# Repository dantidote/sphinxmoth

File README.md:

# Sphinxmoth

### The little board that answers the iSphynxII: a working flash mod for FireWire iPods (1st/2nd gen)

An **active FPGA interposer** that lets flash storage (CF, or SD behind an adapter) fully replace the 1.8″ hard drive in a **1st/2nd-generation
iPod**: boot, standalone playback, **and full-speed FireWire restore + iTunes sync**.

This is the first time in the ~25 years since these iPods shipped
that all of that works at once on flash storage. Passive adapters never could, and
it turns out they never could have. The reason was documented by Texas
Instruments in 2001.

A note on qualifications: I had none. This is the first PCB I've ever had
made, I leaned on the autorouter more than any self-respecting layout
engineer would admit, and before this project I'd never programmed an FPGA.
This board isn't pretty; it was never meant to be. It exists to answer one
question: is this possible at all?

| | |
|---|---|
|  |  |

*The assembled v1 board: FPGA side and CF side. And the point of it all:*

<p align="center"><i>A 1.8 GB file at roughly 15 MB/s over FireWire, through the bridge. No, the
1st gen can't play it. That's not the point.</i></p>

## Buying an assembled board

Sphinxmoth is open source and stays that way: the gerbers, BOM, gateware and
a hardware-validated bitstream are all in this repo, under licenses (MIT and
CERN-OHL-P-2.0) that let you build your own, and sell them if you want to.
Please do.

If you would rather not order a PCB, source a MachXO2, and go find a JTAG
probe, I sell **pre-assembled, pre-flashed boards** at
**[wunkuslabs.com](https://wunkuslabs.com/products/sphinxmoth)**.

## Why the cheap green CF/IDE adapters never worked

FireWire-era iPods (1G/2G, and the 3G) use TI's **TSB43AA82 "iSphynxII"**
FireWire-to-ATA bridge. From TI's own *TSB43AA82 Storage Reference Design*:

> It should be noted that iSphynxII does not implement the 16-bit CRC value
> required at the end of ATA ultraDMA transfers. There are two ways to deal
> with this. The first is to use HDDs that allow transfers to continue even if
> the correct CRC value is not received. The second is to insert an ASIC/PLD
> between iSphynxII and the HDD that calculates the CRC as the transfer is
> taking place and drives it to the drive at the appropriate time. This
> reference design assumes the HDD does not require the CRC.

Apple took TI's first option: the original Toshiba 1.8″ drives tolerate the
missing CRC. **Every CF card enforces it.** So the moment a flash device sees
an Ultra-DMA burst from the iSphynxII, it (correctly) rejects the transfer with
an interface-CRC error, and no passive adapter can ever fix that, because the
CRC simply isn't on the wire.

**This project is the "ASIC/PLD between iSphynxII and the HDD" that TI
described, built 25 years later.** A Lattice MachXO2 sits in the datapath,
re-originates every UDMA burst, and supplies the CRC the iSphynxII omits.

But the CRC is only the first wall. Credit to Reddit user **SquashHour9940**,
whose excellent investigation
([*Further research about flash modified iPod 1st/2nd Gen syncing problem*](https://www.reddit.com/r/ipod/comments/18fujac/further_research_about_flash_modified_ipod_1st2nd/))
independently mapped two more layers:

2. **Removable vs. fixed media**: consumer CF cards report themselves as
   *removable media*; the iPod firmware and iTunes want a *fixed disk*.
   Industrial CF cards (fixed-disk firmware) get past this gate; consumer
   cards don't.
3. **The TSB43AA82 falls back to slow PIO when it detects a CF card**:
   staged 1 MB at a time through the iPod's tiny SRAM, capping passive-adapter
   FireWire transfers around 300 KB/s even when everything else works.

And our bring-up found a fourth layer nobody had hit before, because nobody
had gotten this far:

4. **The PP5002 CPU (the retail OS) is a DMA host too**: its UDMA write
   strobes are electrically hostile (ringing, data-dependent crosstalk) and
   corrupted the filesystem on every standalone boot until this bridge learned
   to detect that master and quietly demote it to PIO.

This bridge defeats all four: it originates the missing CRC, rewrites the
card's IDENTIFY on the wire (media type and DMA capabilities, per master;
a removable or CFA-signature word 0 becomes a classic fixed-disk value,
checksum corrected), keeps the DMA path alive at full speed, and gives
each of the iPod's two very different bus masters the bus discipline it
actually needs. The fixed-disk rewrite has been tested end-to-end with a
retail Lexar Professional 800x (32 GB, UDMA 7), the exact card class the
community documented as removable-reporting: it restores and syncs
through the bridge like any industrial card.

## Status

| | |
|---|---|
| **v1 board** (CF slot, `board/`) | **Working.** Boots, plays, restores, syncs. Reads 19 MB/s, writes 4.6 MB/s over FireWire. Running a 256 GB SD (via FC1307A CF adapter) today. |
| Validated bitstream | `releases/v1.0-first-music/` (build outputs are not run-deterministic; this exact binary is the hardware-proven one) |
| **v2** (native microSD) | **Being considered.** microSD would be nice, but at first glance it needs a larger/more expensive FPGA (the v1 XO2-2000 is 89% full and the disk logic moves on-chip; the draft targets an XO2-7000). Exploratory work lives on the [`v2-native-sd`](../../tree/v2-native-sd) branch: unfabbed, unvalidated, promise-free. **Do not build it.** |

Tested on: iPod 1st gen (firmware 1.5), Transcend industrial 2 GB CF,
FC1307A SD-CF adapter + 256 GB SD, Mac OS X 10.6 + iTunes over FireWire.
2G/3G iPods use the same TSB43AA82 and *should* work; reports welcome.

## Rockbox

Rockbox runs on a Sphinxmoth iPod, with two board-specific wrinkles: the
Rockbox 4.0 release crashes at boot on every 1G/2G (an unaligned store in
the PP5002 scheduler, fixed upstream after 4.0), and Rockbox's stock IDE
timing is too fast for the `v1.1-mg132-fix3b` bridge image, which adds
about 45 ns to every register read through its PIO synchroniser (init fails
with `ATA error: -11` or `-32`). Newer bridge images pass PIO through the
raw pads and need nothing but the crash fix.

Everything Rockbox-related lives in its own repo:
[**rockbox-pp5002-flash**](https://github.com/dantidote/rockbox-pp5002-flash):
the ATA driver patch, tested builds for boards already in the field on
fix3b, and a workflow that rebuilds them on each upstream Rockbox release.
The same files are served from [wunkuslabs.com/guide](https://wunkuslabs.com/guide#rockbox).

## How it works (the short version)

The FPGA discovered during bring-up that it serves **three masters**, and it
gives each a different personality:

| Master | How it's detected | What it gets |
|---|---|---|
| **iSphynxII** (FireWire) | never issues `EXECUTE DIAGNOSTIC` | Full UDMA2 bridge: bursts re-timed through a FIFO, **end-of-burst CRC generated**, multi-burst writes, a deliberately "bouncy" flow-control throttle (it abandons bursts on long clean pauses) |
| **PP5002** (retail OS) | opens with `C90 EXECUTE DIAGNOSTIC` | IDENTIFY patched in flight (DMA capability words zeroed, checksum fixed) → the OS falls back to PIO `READ/WRITE MULTIPLE` through a transparent passthrough |
| **CF card** | n/a | Always runs UDMA2, regardless of what either host negotiated (`SET FEATURES` sector-count byte rewritten on the wire) |

Plus the small in-flight surgeries each master demanded: BSY served for status
polls mid-command, CS/DA forced idle at the card during bridged bursts, strict
data setup/hold on every strobe edge, spec-ordered burst termination, and
STANDBY/SLEEP commands rewritten to CHECK POWER MODE (retail cards honor them,
then never wake the way the OS expects; the original drive woke transparently). The
testbenches encode all of it: the card model sector-terminates, pauses,
checks CRC and enforces tSS; the host model parks on the status register,
polls, and rings its strobe line. Every cruelty in the sims reproduced a bug
first found on real hardware during a two-day, fourteen-bug bring-up.

## Building it

Or skip it: assembled, flashed and tested boards are
[for sale](https://wunkuslabs.com/products/sphinxmoth).

**Board (v1):** upload `board/ipod-cf-udma-gerbers.zip` to any fab (2 layer,
53×72 mm, 1.6 or 0.8 mm). CF socket (J2) is on the BACK; everything else on
the front. `board/BOM.csv` + `board/ipod-cf-udma-pos.csv` for assembly.

**Bitstream:** Lattice Diamond 3.14, `cd diamond && pnmainc rebuild.tcl` →
`impl1/ipodboard_impl1.jed`. Or just flash `releases/v1.0-first-music/`.

**Programming:** Tag-Connect TC2030-IDC-NL pads (J3, zero height) to any
JTAG probe Diamond Programmer / openFPGALoader speaks. The MachXO2 configures
from internal flash; program once, done.

**Power:** bus-powered from the iPod's 3.3 V. J6 shunt selects iPod (1-2) or
bench USB-C (2-3); never both. The green LED blips a slow heartbeat when idle
and flashes while data is moving through the bridge. The UART header (J5, 115200 8N1) streams the
gateware's event log; if something misbehaves, that log is the microscope
this whole project was debugged through.

**Simulation:** Icarus Verilog: `cd gateware && iverilog -g2012 -DSIM -I rtl
-o wr.vvp sim/tb_full_write.v rtl/*.v && vvp wr.vvp` (likewise
`tb_full_read.v`).

## Repository layout

| Path | Contents |
|---|---|
| `board/` | v1 board: KiCad project, fabbed gerbers, BOM, schematic PDF, DRC/ERC |
| `gateware/rtl/` | the bridge RTL (`interposer_top` + engines) |
| `gateware/sim/` | hardware-calibrated torture testbenches |
| `diamond/` | Lattice Diamond build project |
| `releases/` | hardware-validated bitstreams |
| `v2-native-sd` branch | exploratory native-microSD v2: board draft, `ata_device`/`sd_host` cores, design doc |

## Known v1 errata

- J2 pin 39 (−CSEL) must be grounded (already fixed in these gerbers).
- J2 pins 45/46 (−DASP/−PDIAG) float; some cards may care (10 k pull-ups to
  3.3 V recommended).
- The USB-C shield holes share the CF socket's courtyard; desoldering J4
  heat-stresses socket joints (ask us how we know). v2 deletes both parts.
- DD-bus ↔ control-line crosstalk exists at the margins; the gateware routes
  around it (PIO for the PP5002), v2 adds proper guarding.

## Credits

- **SquashHour9940** (r/ipod): the fixed-disk/removable-media and
  TSB43AA82-PIO-fallback research that mapped layers 2 and 3:
  https://www.reddit.com/r/ipod/comments/18fujac/further_research_about_flash_modified_ipod_1st2nd/
- Texas Instruments, for documenting in 2001 exactly which chip to blame
  and exactly what to build about it.
- [freerouting](https://github.com/freerouting/freerouting): the open-source
  autorouter that closed every net on both boards.

## License

Gateware and software: MIT. Hardware (schematics, board files, gerbers):
CERN-OHL-P-2.0. No warranty; a 25-year-old iPod is involved.

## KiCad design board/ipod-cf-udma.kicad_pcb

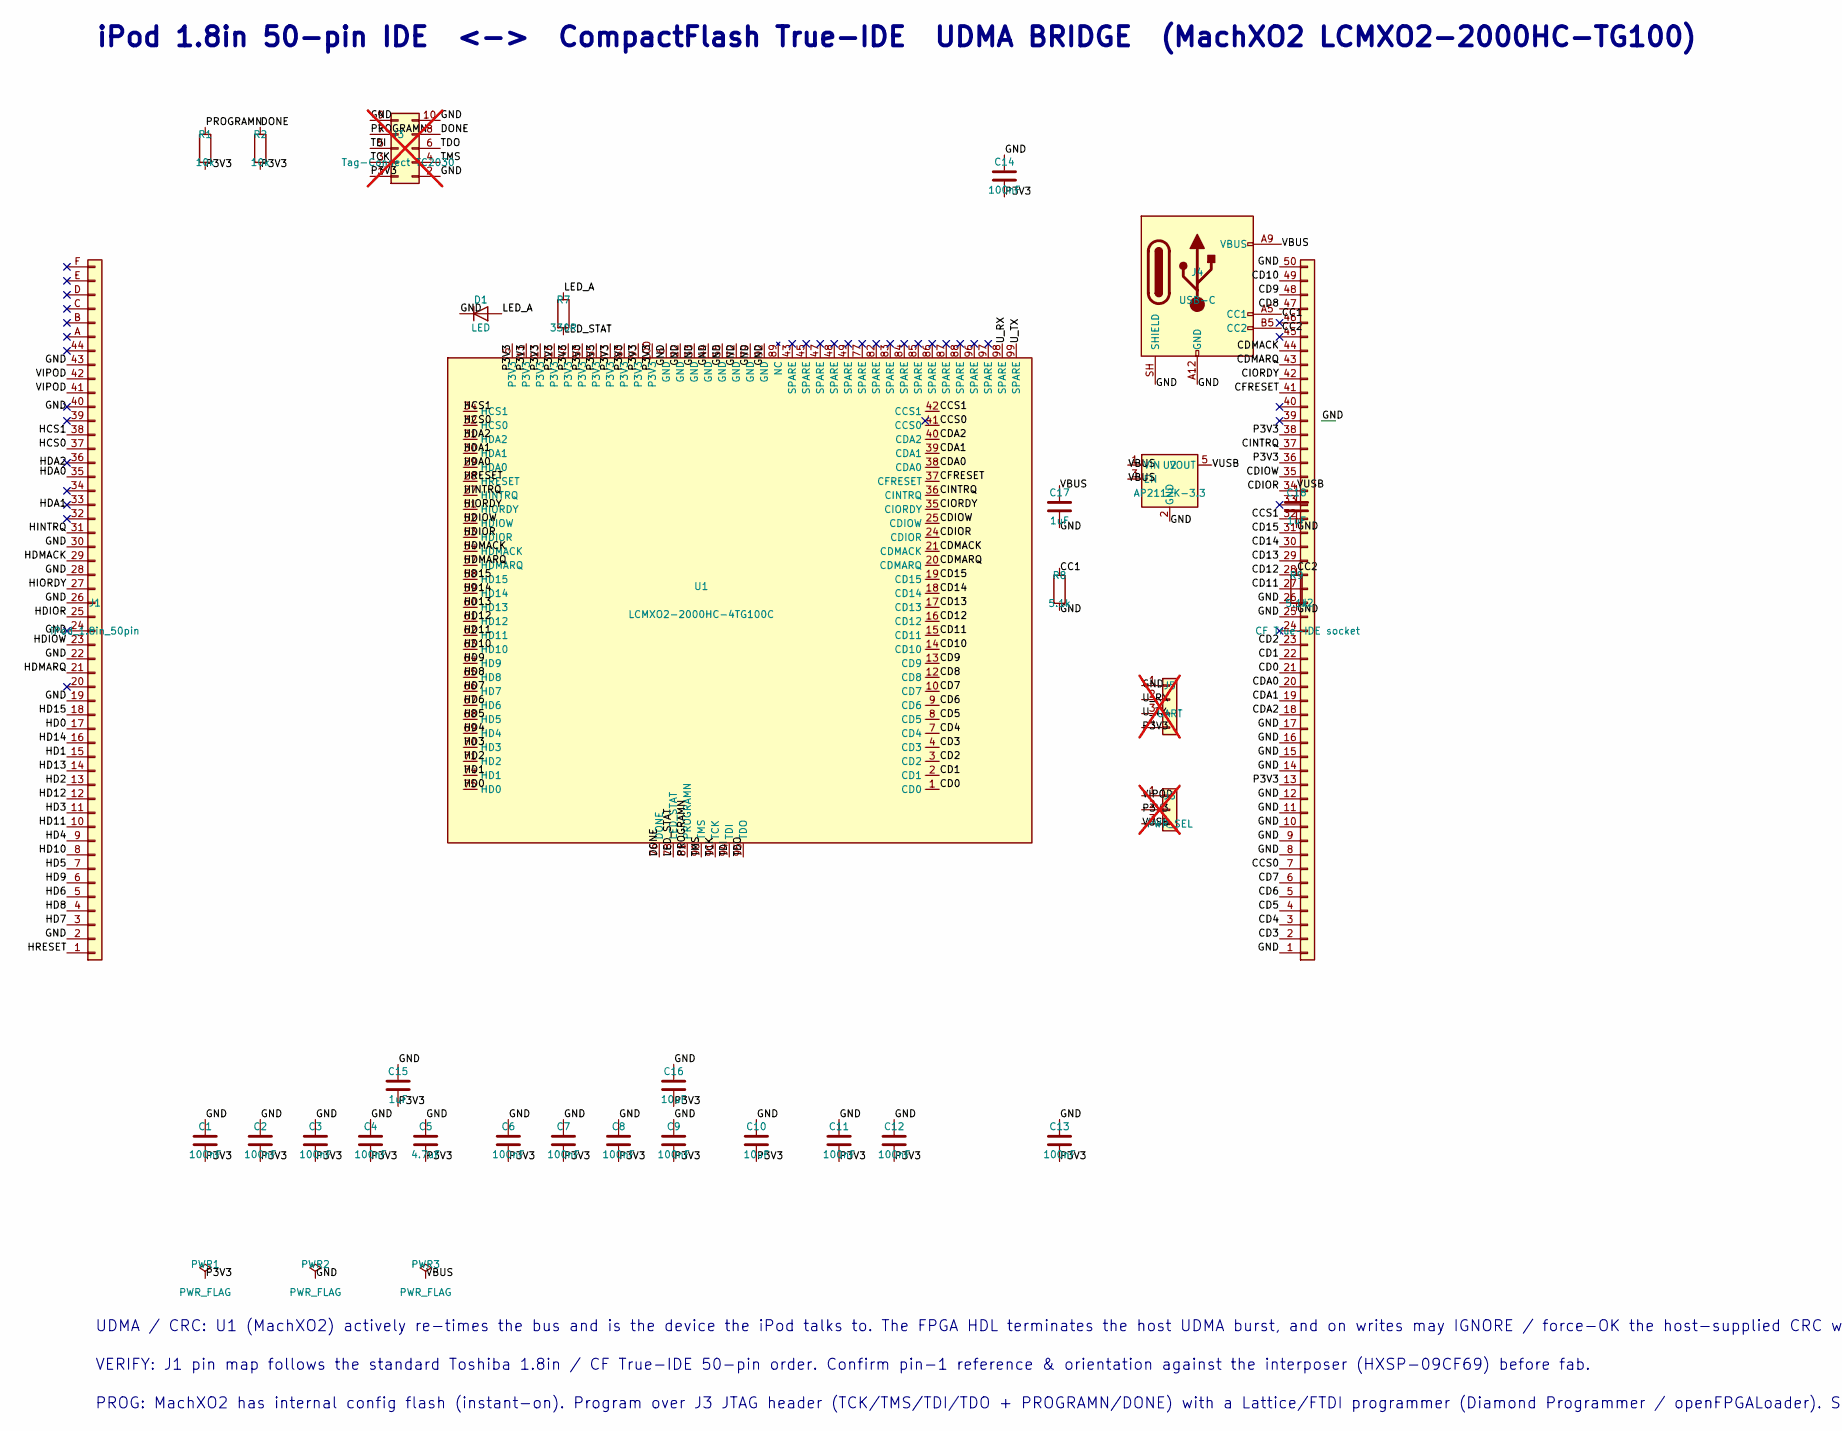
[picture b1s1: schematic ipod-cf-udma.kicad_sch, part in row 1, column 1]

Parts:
C1, C2, C3, C4, C6, C7, C8, C9, C11, C12, C13, C14: 100nF; C_0402_1005Metric; MPN CL05B104KO5NNNC
C5: 4.7uF; C_0603_1608Metric; MPN CL10A475KO8NNNC
C10, C16: 10uF; C_0805_2012Metric; MPN C2012X5R1E106K125AB
C15, C17, C18: 1uF; C_0402_1005Metric; MPN CL05A105KA5NNNC
D1: LED; LED_0603_1608Metric; MPN 150060GS75000
J1: iPod_1.8in_50pin; MPN SPECIALTY-iPod-1.8in-50pin
J2: CF True-IDE socket; CF-Card_3M_N7E50-E516xx-30; MPN N7E50-E516PK-30
J3: Tag-Connect TC2030; Tag-Connect_TC2030-IDC-NL_2x03_P1.27mm_Vertical; MPN DNP-padsonly; not fitted
J4: USB-C; USB_C_Receptacle_GCT_USB4125-xx-x_6P_TopMnt_Horizontal; MPN USB4125-GF-A-0190
J5: UART; PinHeader_1x04_P1.27mm_Vertical_SMD_Pin1Left; MPN DNP-optional-header; not fitted
J6: PWR_SEL; PinHeader_1x03_P1.27mm_Vertical_SMD_Pin1Left; MPN DNP-solderjumper; not fitted
PWR1, PWR2, PWR3: PWR_FLAG
R1, R2: 10k; R_0402_1005Metric; MPN CRCW040210K0FKED
R7: 330R; R_0402_1005Metric; MPN RC0402FR-07330RL
R8, R9: 5.1k; R_0402_1005Metric; MPN RC0402FR-075K1L
U1: LCMXO2-2000HC-4TG100C; TQFP-100_14x14mm_P0.5mm; MPN LCMXO2-2000HC-4TG100C
U2: AP2112K-3.3; SOT-23-5; MPN AP2112K-3.3TRG1

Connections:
CC1: J4.A5 (CC1), R8.1
CC2: J4.B5 (CC2), R9.1
CCS0: J2.7, U1.41 (CCS0)
CCS1: J2.32, U1.42 (CCS1)
CD0: J2.21, U1.1 (CD0)
CD1: J2.22, U1.2 (CD1)
CD2: J2.23, U1.3 (CD2)
CD3: J2.2, U1.4 (CD3)
CD4: J2.3, U1.7 (CD4)
CD5: J2.4, U1.8 (CD5)
CD6: J2.5, U1.9 (CD6)
CD7: J2.6, U1.10 (CD7)
CD8: J2.47, U1.12 (CD8)
CD9: J2.48, U1.13 (CD9)
CD10: J2.49, U1.14 (CD10)
CD11: J2.27, U1.15 (CD11)
CD12: J2.28, U1.16 (CD12)
CD13: J2.29, U1.17 (CD13)
CD14: J2.30, U1.18 (CD14)
CD15: J2.31, U1.19 (CD15)
CDA0: J2.20, U1.38 (CDA0)
CDA1: J2.19, U1.39 (CDA1)
CDA2: J2.18, U1.40 (CDA2)
CDIOR: J2.34, U1.24 (CDIOR)
CDIOW: J2.35, U1.25 (CDIOW)
CDMACK: J2.44, U1.21 (CDMACK)
CDMARQ: J2.43, U1.20 (CDMARQ)
CFRESET: J2.41, U1.37 (CFRESET)
CINTRQ: J2.37, U1.36 (CINTRQ)
CIORDY: J2.42, U1.35 (CIORDY)
DONE: J3.8, R2.1, U1.76 (DONE)
GND: C1.1, C2.1, C3.1, C4.1, C5.1, C6.1, C7.1, C8.1, C9.1, C10.1, C11.1, C12.1, C13.1, C14.1, C15.1, C16.1, C17.2, C18.2, D1.1 (K), J1.2, J1.19, J1.22, J1.24, J1.26, J1.28, J1.30, J1.40, J1.43, J2.1, J2.8, J2.9, J2.10, J2.11, J2.12, J2.14, J2.15, J2.16, J2.17, J2.25, J2.26, J2.39, J2.50, J3.2, J3.9, J3.10, J4.A12 (GND), J4.B12 (GND), J4.SH (SHIELD), J5.1, PWR2.1, R8.2, R9.2, U1.6 (GND), U1.22 (GND), U1.33 (GND), U1.44 (GND), U1.56 (GND), U1.72 (GND), U1.79 (GND), U1.92 (GND), U2.2 (GND)
HCS0: J1.37, U1.32 (HCS0)
HCS1: J1.38, U1.34 (HCS1)
HD0: J1.17, U1.75 (HD0)
HD1: J1.15, U1.74 (HD1)
HD2: J1.13, U1.71 (HD2)
HD3: J1.11, U1.70 (HD3)
HD4: J1.9, U1.69 (HD4)
HD5: J1.7, U1.68 (HD5)
HD6: J1.5, U1.67 (HD6)
HD7: J1.3, U1.66 (HD7)
HD8: J1.4, U1.65 (HD8)
HD9: J1.6, U1.64 (HD9)
HD10: J1.8, U1.63 (HD10)
HD11: J1.10, U1.62 (HD11)
HD12: J1.12, U1.61 (HD12)
HD13: J1.14, U1.60 (HD13)
HD14: J1.16, U1.59 (HD14)
HD15: J1.18, U1.58 (HD15)
HDA0: J1.35, U1.29 (HDA0)
HDA1: J1.33, U1.30 (HDA1)
HDA2: J1.36, U1.31 (HDA2)
HDIOR: J1.25, U1.53 (HDIOR)
HDIOW: J1.23, U1.52 (HDIOW)
HDMACK: J1.29, U1.54 (HDMACK)
HDMARQ: J1.21, U1.57 (HDMARQ)
HINTRQ: J1.31, U1.27 (HINTRQ)
HIORDY: J1.27, U1.51 (HIORDY)
HRESET: J1.1, U1.28 (HRESET)
LED_A: D1.2 (A), R7.1
LED_STAT: R7.2, U1.78 (LED_STAT)
P3V3: C1.2, C2.2, C3.2, C4.2, C5.2, C6.2, C7.2, C8.2, C9.2, C10.2, C11.2, C12.2, C13.2, C14.2, C15.2, C16.2, J2.13, J2.36, J2.38, J3.1, J5.4, J6.2, PWR1.1, R1.2, R2.2, U1.5 (P3V3), U1.11 (P3V3), U1.23 (P3V3), U1.26 (P3V3), U1.46 (P3V3), U1.50 (P3V3), U1.55 (P3V3), U1.73 (P3V3), U1.80 (P3V3), U1.93 (P3V3), U1.100 (P3V3)
PROGRAMN: J3.7, R1.1, U1.81 (PROGRAMN)
TCK: J3.3, U1.91 (TCK)
TDI: J3.5, U1.94 (TDI)
TDO: J3.6, U1.95 (TDO)
TMS: J3.4, U1.90 (TMS)
U_RX: J5.2, U1.98 (SPARE)
U_TX: J5.3, U1.99 (SPARE)
VBUS: C17.1, J4.A9 (VBUS), J4.B9 (VBUS), PWR3.1, U2.1 (VIN), U2.3 (EN)
VIPOD: J1.41, J1.42, J6.1
VUSB: C18.1, J6.3, U2.5 (VOUT)

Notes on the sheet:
iPod 1.8in 50-pin IDE <-> CompactFlash True-IDE UDMA BRIDGE (MachXO2 LCMXO2-2000HC-TG100)
UDMA / CRC: U1 (MachXO2) actively re-times the bus and is the device the iPod talks to. The FPGA HDL terminates the host UDMA burst, and on writes may IGNORE / force-OK the host-supplied CRC while regenerating a correct CRC toward the CF card. A purely passive adapter CANNOT do this - that is why a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
VERIFY: J1 pin map follows the standard Toshiba 1.8in / CF True-IDE 50-pin order. Confirm pin-1 reference & orientation against the interposer (HXSP-09CF69) before fab.
PROG: MachXO2 has internal config flash (instant-on). Program over J3 JTAG header (TCK/TMS/TDI/TDO + PROGRAMN/DONE) with a Lattice/FTDI programmer (Diamond Programmer / openFPGALoader). Single 3.3V rail, bus-powered from host (J1.13/38). I/O pin assignment is a starting point - lock final pins in D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

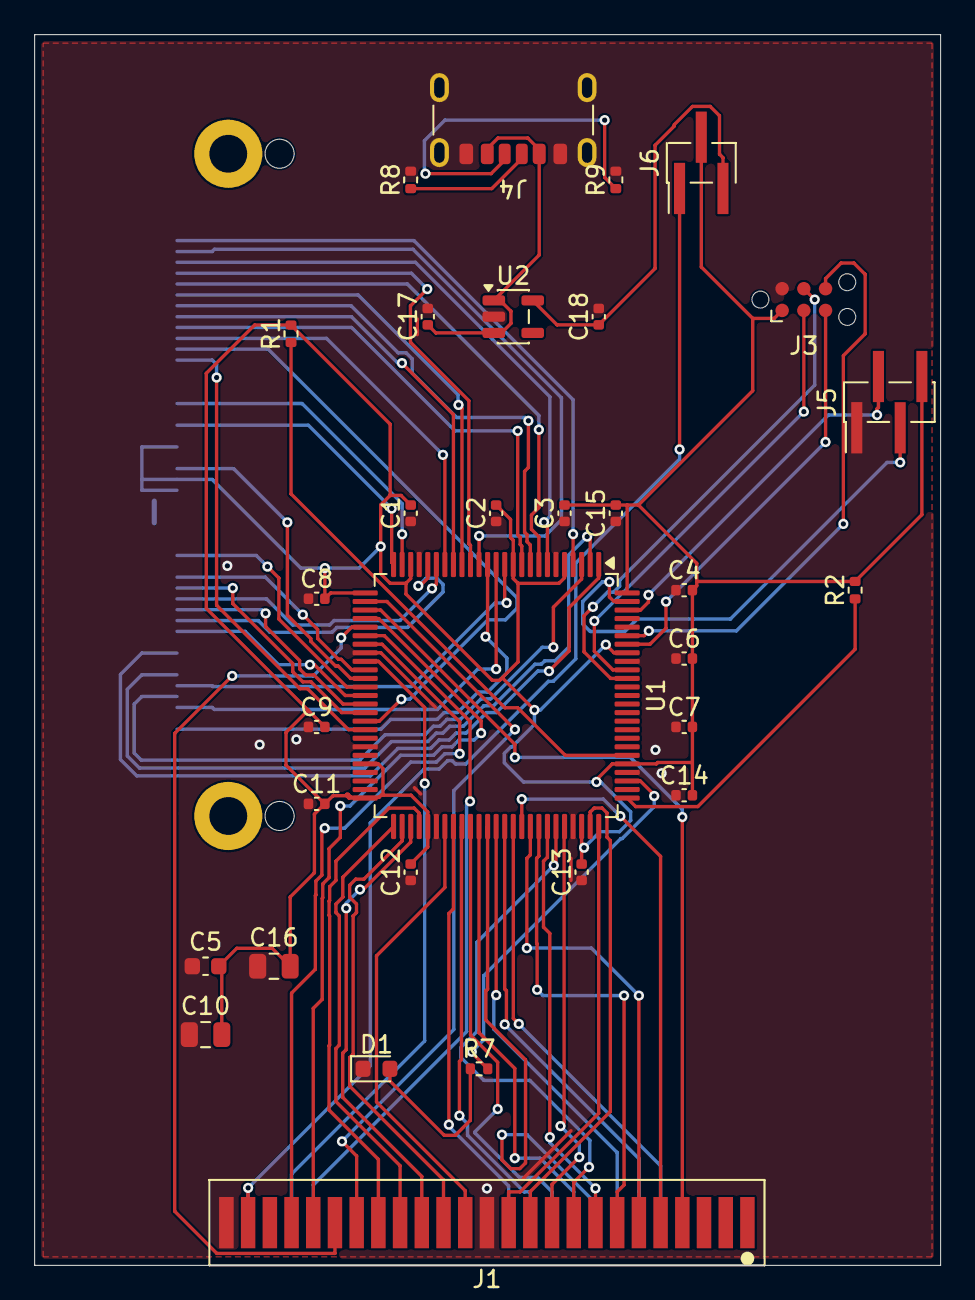
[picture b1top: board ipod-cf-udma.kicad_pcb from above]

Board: 2 copper layers, 53.0 x 72.0 mm, 32 parts (1 on the bottom side), 73 nets.

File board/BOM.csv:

"Refs","Value","Footprint","MPN","Qty"
"C1-C4,C6-C9,C11-C14","100nF","Capacitor_SMD:C_0402_1005Metric","CL05B104KO5NNNC","12"
"C5","4.7uF","Capacitor_SMD:C_0603_1608Metric","CL10A475KO8NNNC","1"
"C10,C16","10uF","Capacitor_SMD:C_0805_2012Metric","C2012X5R1E106K125AB","2"
"C15,C17,C18","1uF","Capacitor_SMD:C_0402_1005Metric","CL05A105KA5NNNC","3"
"D1","LED","LED_SMD:LED_0603_1608Metric","150060GS75000","1"
"J1","iPod_1.8in_50pin","interposer:iPod_1.8in_50pin","SPECIALTY-iPod-1.8in-50pin","1"
"J2","CF True-IDE socket","Connector_Card:CF-Card_3M_N7E50-E516xx-30","N7E50-E516PK-30","1"
"J4","USB-C","Connector_USB:USB_C_Receptacle_GCT_USB4125-xx-x_6P_TopMnt_Horizontal","USB4125-GF-A-0190","1"
"R1,R2","10k","Resistor_SMD:R_0402_1005Metric","CRCW040210K0FKED","2"
"R7","330R","Resistor_SMD:R_0402_1005Metric","RC0402FR-07330RL","1"
"R8,R9","5.1k","Resistor_SMD:R_0402_1005Metric","RC0402FR-075K1L","2"
"U1","LCMXO2-2000HC-4TG100C","Package_QFP:TQFP-100_14x14mm_P0.5mm","LCMXO2-2000HC-4TG100C","1"
"U2","AP2112K-3.3","Package_TO_SOT_SMD:SOT-23-5","AP2112K-3.3TRG1","1"

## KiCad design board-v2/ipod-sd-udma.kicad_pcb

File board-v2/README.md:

# ipod-sd-udma - v2 board (native microSD, compact 4-layer)

The v2 realization of [docs/v2-native-sd.md](../docs/v2-native-sd.md): the CF
socket is gone, the FPGA *is* the disk, sectors live on a microSD card, and
the board is as small and as simple as it can be. Derived **entirely by
script** from the proven v1 board - the flow below replays from
`../ipod-cf-udma.kicad_pcb`.

```
 iPod 1.8" 50-pin (J1)  <->  LCMXO2-7000HC-4TG144 (U1, front)  <->  microSD (J2, back)
```

* **38 × 36 mm, 4-layer** - down from v1's 53 × 72 mm 2-layer (48% of the area).
* **microSD on the BACK**, stacked under the FPGA, card slot at the top edge.
* **0 unconnected, 0 electrical DRC violations.** (Two copper-to-edge items
  remain: the microSD's shield tabs at the top edge, inherent to a socket that
  sits at the board edge for card insertion - v1 shipped the identical benign
  overlap on its CF socket.)

## The whole BOM

| Ref | Part | Side |
|---|---|---|
| U1 | LCMXO2-7000HC-4TG144C - the only active component | front |
| J1 | iPod 50-pin card edge (custom fp, v1-proven, untouched) | edge |
| J2 | Hirose DM3AT-SF-PEJM5 microSD push-push | back |
| J3 | Tag-Connect TC2030 pads (JTAG) | front |
| J5 | 4-pin 1.27 mm **through-hole** UART header (v1 errata #3) | front |
| C1–C16 | 12× 100 nF + 4.7 µF + 2× 10 µF + 1 µF, all decoupling | back |

Zero resistors, zero LEDs, zero regulators, no USB. What got deleted vs v1
and why it's safe:

* **USB-C + LDO + J6 source select** - single supply: the iPod's 3.3 V IS the
  rail. Bench power for bring-up: J5 pin 4 or TC2030 pad 1.
* **SD series resistors** - 16.6 MHz over ~2 cm; LPF drive/slew does the job.
* **PROGRAMN/DONE pull-ups (R1/R2)** - plain user I/O with SYSCONFIG off;
  JTAG_PORT=ENABLE is the recovery path.
* **Heartbeat LED (D1/R7)** - the UART `B=B0` boot banner is the alive-signal.
* **CF strapping saga** - gone with the socket. Card-detect switch feeds
  SD_CD_N; no card ⇒ the ATA face holds BSY.

## Why 4 layers

A 144-pin 0.5 mm QFP with 100+ signals in a compact outline is beyond a clean
2-layer route (v1 got away with 2 layers only because it was a 100-pin part on
a board 3× the size). The stackup is **Sig / GND / 3V3 / Sig**: dedicated inner
GND + 3V3 planes turn signal routing back into a 2-layer problem (both outer
layers reference a plane) and every power/GND pin vias straight to its plane -
no power traces, no stitching drama. 4 layers is a fab attribute; the BOM is
unchanged.

## FPGA pin assignment

Geometry-driven (`assign_pins.py`, the v1 trick): the FPGA's I/O pins are
free, so they're paired **in order** to the connector fanout - HD0–15 map to
U1's bottom-edge pins in the same x-order as J1's fingers, SD to the top edge,
UART to the left. That crossing-free fanout is what makes the compact board
routable. The LPF (`../diamond-sd/ipodboard_sd.lpf`) is back-annotated to
match, and Diamond closes timing at **67.1 MHz** (vs 66.5 needed) with it.
Supply map cross-validated three ways (Diamond PAD + spreadsheet + DS Table
4.6): 12 GND, 4 VCC, 12 VCCIO, pin 129 NC. Full table: `tg144_pins.csv`.

## Flow (all rerunnable)

| Step | File |
|---|---|
| derive + place (outline, 4-layer, flip parts to back) | `build_v2.py` |
| geometry pin assignment + LPF back-annotation | `assign_pins.py` |
| Specctra DSN export / SES import | `route_v2.py` |
| freerouting with a fail-fast load-hang guard | `fr.sh` |
| rip stuck signal nets & re-export (if needed) | `riproute.py` |
| hand-route residual congested nets | `hand_route.py` |
| stitch any power pad the router missed | `stitch_v2.py` |
| gerbers/drill/pos + renders / BOM | `finalize_v2.sh` / `gen_bom.py` |

Typical run: `build_v2 → assign_pins → route_v2 export → fr.sh 80 →
route_v2 import → DRC`. freerouting closes all 121 nets (signals + power-to-
plane) in seconds on the 4-layer board; only occasionally does it need a
`hand_route`/`stitch` top-up.

## Bring-up notes

* Gateware: `../diamond-sd/` → `impl1/ipodboard_sd_impl1.jed`, flash via
  Diamond Programmer + TC2030 on J3.
* `SD_FAST=0` for first silicon (16.6 MHz SD clock, fat margins); enable the
  33.25 MHz CMD6 high-speed path only after scoping DAT.
* UART logger (J5) speaks the v1 5-char event language - `M`/`m` = SD init
  ok/fail, `G` = SD retry counter, `B=B0` = board alive.

## Schematic

Not redrawn - `build_v2.py` + `assign_pins.py` (and the LPF) are the netlist
ground truth. Redraw `ipod-sd-udma.kicad_sch` from the board before a respin
if schematic-parity matters.

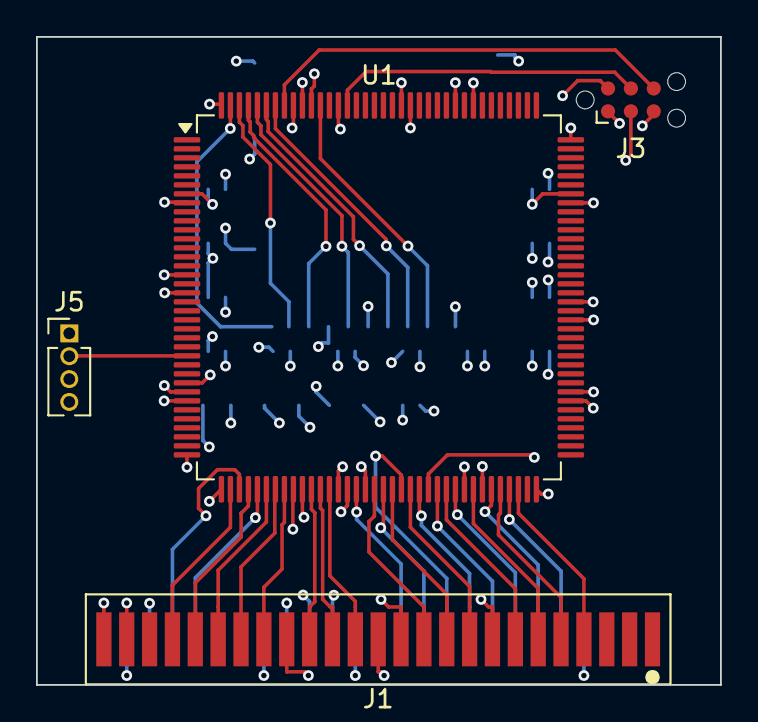
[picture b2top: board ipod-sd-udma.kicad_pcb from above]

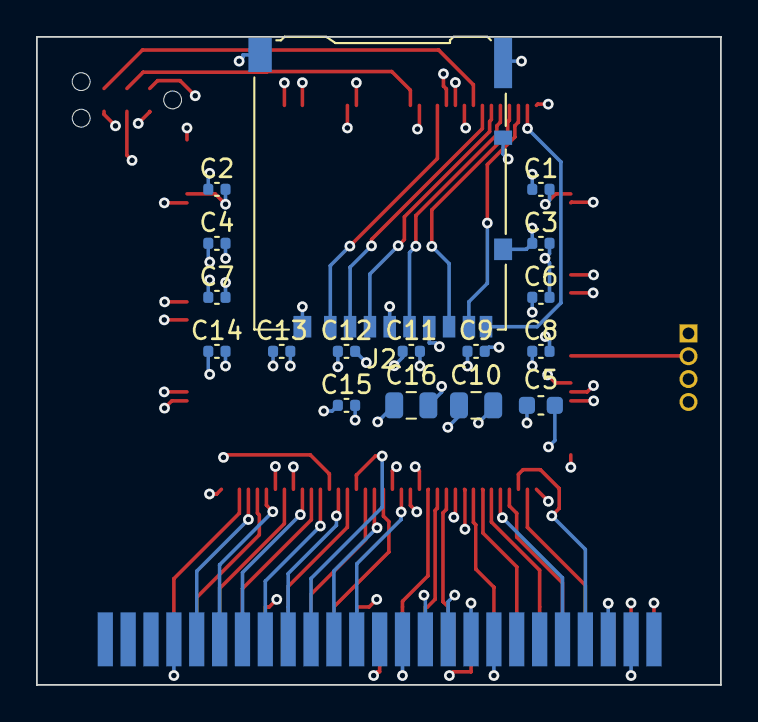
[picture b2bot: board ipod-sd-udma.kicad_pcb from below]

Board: 4 copper layers, 38.0 x 36.0 mm, 21 parts (17 on the bottom side), 43 nets.

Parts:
C1, C2, C3, C4, C6, C7, C8, C9, C11, C12, C13, C14: 100nF; C_0402_1005Metric
C5: 4.7uF; C_0603_1608Metric
C10, C16: 10uF; C_0805_2012Metric
C15: 1uF; C_0402_1005Metric
J1: iPod 1.8in 50-pin; iPod_1.8in_50pin
J2: microSD DM3AT-SF-PEJM5; microSD_HC_Hirose_DM3AT-SF-PEJM5
J3: TC2030; Tag-Connect_TC2030-IDC-NL_2x03_P1.27mm_Vertical
J5: UART; PinHeader_1x04_P1.27mm_Vertical
U1: LCMXO2-7000HC-4TG144C; TQFP-144_20x20mm_P0.5mm

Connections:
GND: C1.1, C2.1, C3.1, C4.1, C5.1, C6.1, C7.1, C8.1, C9.1, C10.1, C11.1, C12.1, C13.1, C14.1, C15.1, C16.1, J1.2, J1.19, J1.22, J1.24, J1.26, J1.28, J1.30, J1.40, J1.43, J2.6, J2.10, J2.SH, J3.2, J5.1, U1.8, U1.18, U1.29, U1.46, U1.53, U1.64, U1.80, U1.90, U1.101, U1.116, U1.124, U1.134
HCS0: J1.37, U1.38
HCS1: J1.38, U1.39
HD0: J1.17, U1.50
HD1: J1.15, U1.54
HD2: J1.13, U1.56
HD3: J1.11, U1.58
HD4: J1.9, U1.60
HD5: J1.7, U1.62
HD6: J1.5, U1.65
HD7: J1.3, U1.68
HD8: J1.4, U1.69
HD9: J1.6, U1.67
HD10: J1.8, U1.63
HD11: J1.10, U1.61
HD12: J1.12, U1.59
HD13: J1.14, U1.57
HD14: J1.16, U1.55
HD15: J1.18, U1.52
HDA0: J1.35, U1.40
HDA1: J1.33, U1.42
HDA2: J1.36, U1.41
HDIOR: J1.25, U1.47
HDIOW: J1.23, U1.48
HDMACK: J1.29, U1.44
HDMARQ: J1.21, U1.49
HINTRQ: J1.31, U1.43
HIORDY: J1.27, U1.45
HRESET: J1.1, U1.70
P3V3: C1.2, C2.2, C3.2, C4.2, C5.2, C6.2, C7.2, C8.2, C9.2, C10.2, C11.2, C12.2, C13.2, C14.2, C15.2, C16.2, J1.41, J1.42, J2.4, J3.1, J5.4, U1.7, U1.16, U1.30, U1.36, U1.37, U1.51, U1.66, U1.72, U1.79, U1.88, U1.102, U1.108, U1.118, U1.123, U1.135, U1.144
SDCD: J2.9, U1.143
SDCLK: J2.5, U1.140
SDCMD: J2.3, U1.139
SDD0: J2.7, U1.141
SDD1: J2.8, U1.142
SDD2: J2.1, U1.133
SDD3: J2.2, U1.138
TCK: J3.3, U1.131
TDI: J3.5, U1.136
TDO: J3.6, U1.137
TMS: J3.4, U1.130
U_RX: J5.2, U1.25
U_TX: J5.3, U1.28

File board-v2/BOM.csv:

"Refs","Value","Footprint","MPN","Qty"
"C10,C16","10uF","Capacitor_SMD:C_0805_2012Metric","C2012X5R1E106K125AB","2"
"C1-C4,C6-C9,C11-C14","100nF","Capacitor_SMD:C_0402_1005Metric","CL05B104KO5NNNC","12"
"C15","1uF","Capacitor_SMD:C_0402_1005Metric","CL05A105KA5NNNC","1"
"C5","4.7uF","Capacitor_SMD:C_0603_1608Metric","CL10A475KO8NNNC","1"
"J1","iPod 1.8in 50-pin","interposer:iPod_1.8in_50pin","","1"
"J2","microSD DM3AT-SF-PEJM5","microSD_HC_Hirose_DM3AT-SF-PEJM5","DM3AT-SF-PEJM5","1"
"J3","TC2030","Tag-Connect_TC2030-IDC-NL_2x03_P1.27mm_Vertical","","1"
"J5","UART","PinHeader_1x04_P1.27mm_Vertical","20021311-00004T4LF","1"
"U1","LCMXO2-7000HC-4TG144C","TQFP-144_20x20mm_P0.5mm","LCMXO2-7000HC-4TG144C","1"
